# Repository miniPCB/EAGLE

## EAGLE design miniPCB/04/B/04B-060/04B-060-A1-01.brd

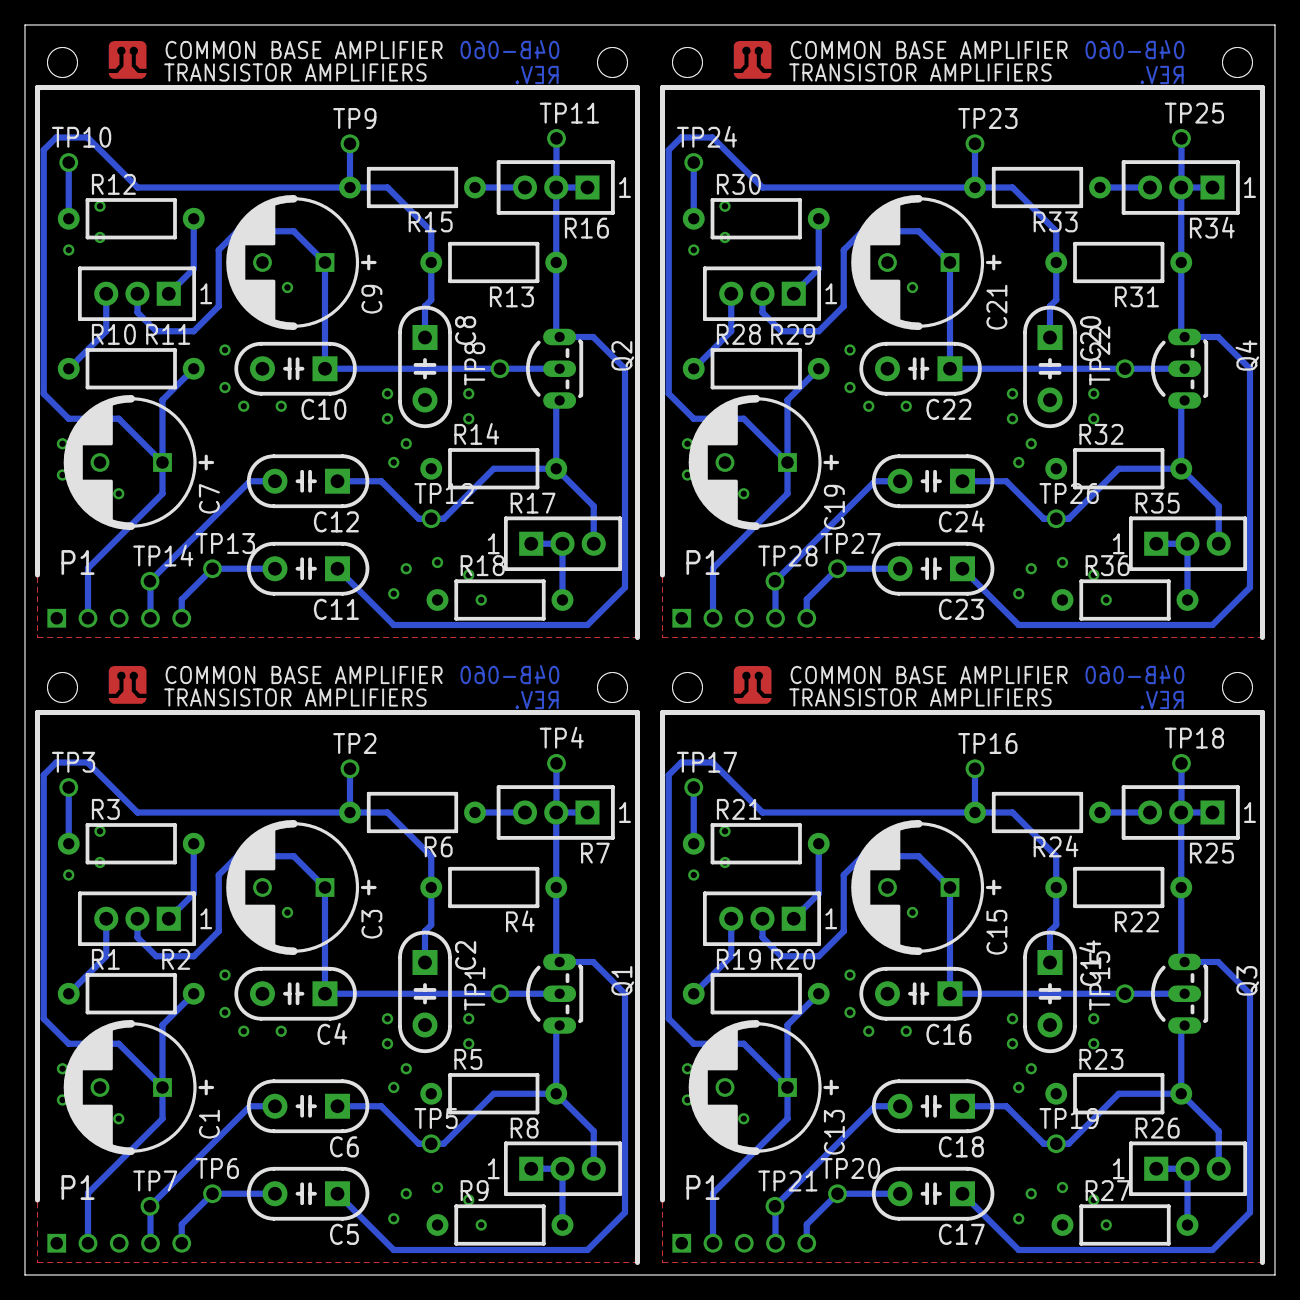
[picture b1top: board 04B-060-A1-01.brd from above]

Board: 2 copper layers, 100.0 x 100.0 mm, 100 parts (0 on the bottom side), 44 nets.

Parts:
C1, C3, C7, C9, C13, C15, C19, C21: C5MM
C2, C4, C5, C6, C8, C10, C11, C12, C14, C16, C17, C18, C20, C22, C23, C24: C050-024X044
P1, P2, P3, P4: PINS_1X5
PCB1, PCB2, PCB3, PCB4: MINIPCB_0P_50X50MM
Q1, Q2, Q3, Q4: NPN; TO92-EBC-OVAL
R1, R3, R4, R5, R6, R9, R10, R12, R13, R14, R15, R18, R19, R21, R22, R23, R24, R27, R28, R30, R31, R32, R33, R36: 0204/10
R2, R7, R8, R11, R16, R17, R20, R25, R26, R29, R34, R35: TRIM_0100
TP1, TP2, TP3, TP4, TP5, TP6, TP7, TP8, TP9, TP10, TP11, TP12, TP13, TP14, TP15, TP16, TP17, TP18, TP19, TP20, TP21, TP22, TP23, TP24, TP25, TP26, TP27, TP28: PINS_1_TESTPOINT_KE5000_NOTEXT

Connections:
BASE: C3.+, C4.1, Q1.B, R2.2, TP1.1
BASE1: C9.+, C10.1, Q2.B, R11.2, TP8.1
BASE2: C15.+, C16.1, Q3.B, R20.2, TP15.1
BASE3: C21.+, C22.1, Q4.B, R29.2, TP22.1
COLLECTOR: C5.1, Q1.C, R4.1, R7.1, R7.2, TP4.1
COLLECTOR1: C11.1, Q2.C, R13.1, R16.1, R16.2, TP11.1
COLLECTOR2: C17.1, Q3.C, R22.1, R25.1, R25.2, TP18.1
COLLECTOR3: C23.1, Q4.C, R31.1, R34.1, R34.2, TP25.1
EMITTER: C6.1, Q1.E, R5.2, R8.3, TP5.1
EMITTER1: C12.1, Q2.E, R14.2, R17.3, TP12.1
EMITTER2: C18.1, Q3.E, R23.2, R26.3, TP19.1
EMITTER3: C24.1, Q4.E, R32.2, R35.3, TP26.1
GND: C1.-, C2.2, C3.-, C4.2, P1.1, R3.1, R5.1, R9.1, TP3.1
GND1: C7.-, C8.2, C9.-, C10.2, P2.1, R12.1, R14.1, R18.1, TP10.1
GND2: C13.-, C14.2, C15.-, C16.2, P3.1, R21.1, R23.1, R27.1, TP17.1
GND3: C19.-, C20.2, C21.-, C22.2, P4.1, R30.1, R32.1, R36.1, TP24.1
INPUT: C6.2, P1.4, TP7.1
INPUT1: C12.2, P2.4, TP14.1
INPUT2: C18.2, P3.4, TP21.1
INPUT3: C24.2, P4.4, TP28.1
unnamed: R2.1, R3.2
unnamed: R1.1, R2.3
unnamed: R8.1, R8.2, R9.2
unnamed: R6.1, R7.3
unnamed: R11.1, R12.2
unnamed: R10.1, R11.3
unnamed: R15.1, R16.3
unnamed: R17.1, R17.2, R18.2
unnamed: R20.1, R21.2
unnamed: R19.1, R20.3
unnamed: R24.1, R25.3
unnamed: R26.1, R26.2, R27.2
unnamed: R29.1, R30.2
unnamed: R28.1, R29.3
unnamed: R33.1, R34.3
unnamed: R35.1, R35.2, R36.2
OUTPUT: C5.2, P1.5, TP6.1
OUTPUT1: C11.2, P2.5, TP13.1
OUTPUT2: C17.2, P3.5, TP20.1
OUTPUT3: C23.2, P4.5, TP27.1
V+: C1.+, C2.1, P1.2, R1.2, R4.2, R6.2, TP2.1
V+1: C7.+, C8.1, P2.2, R10.2, R13.2, R15.2, TP9.1
V+2: C13.+, C14.1, P3.2, R19.2, R22.2, R24.2, TP16.1
V+3: C19.+, C20.1, P4.2, R28.2, R31.2, R33.2, TP23.1

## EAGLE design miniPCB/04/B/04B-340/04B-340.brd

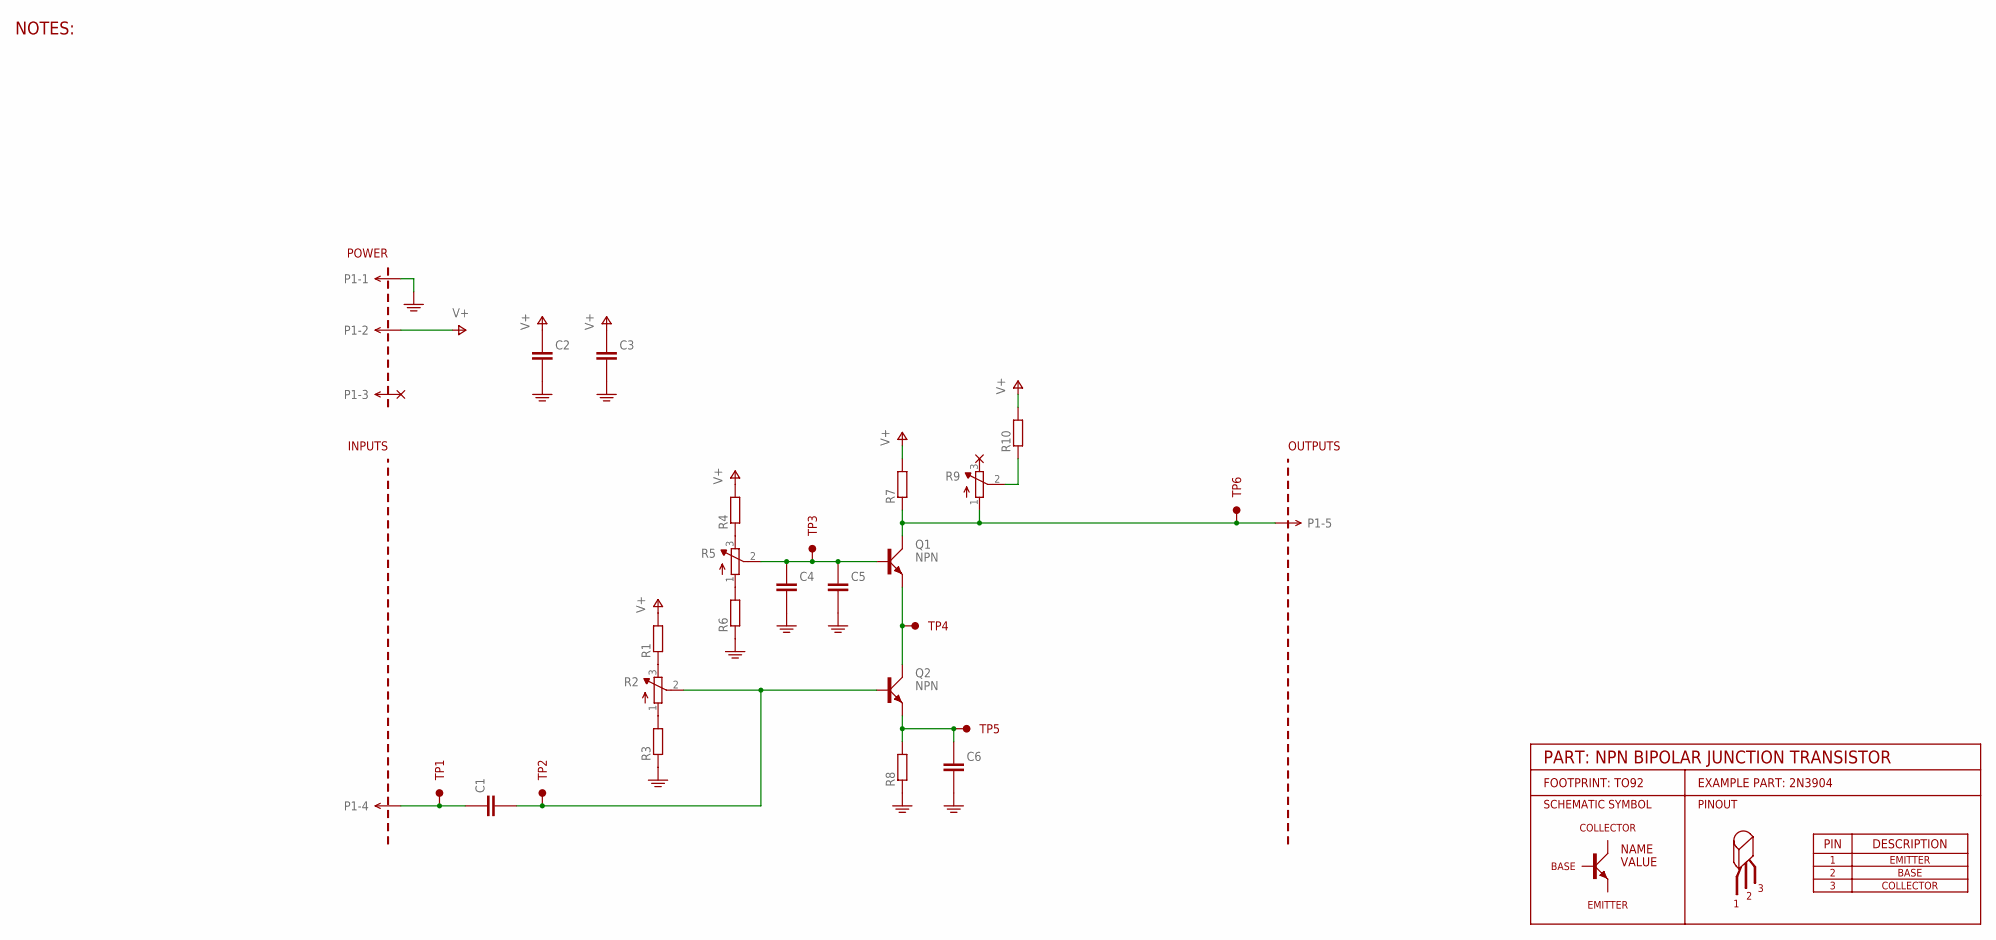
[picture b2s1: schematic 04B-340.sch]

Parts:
C1, C3, C4: CAPACITORTHD; C050-024X044
C2, C5, C6: CAPACITOR_10; C5MM
P1: MINIPCB_5P5P; PINS_1X5
PCB1: MINIPCB_0P50X50; MINIPCB_0P_50X50MM; PART_NUMBER 04B-340
Q1, Q2: NPN; TO92-EBC-OVAL
R1, R3, R4, R6, R7, R8, R10: RESISTORTHD; 0204/10
R2, R5, R9: TRIMPOT0.100THD; TRIM_0100
TP1, TP2, TP3, TP4, TP5, TP6: TESTPOINTKE5000-SMTEXT; PINS_1_TESTPOINT_KE5000_NOTEXT

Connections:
GND: C2.-, C3.2 (-), C4.2 (-), C5.-, C6.-, P1.1, R3.1, R6.1, R8.1
unnamed: R2.1 (A), R3.2
unnamed: C1.2 (-), Q2.B, R2.2 (S), TP2.1
unnamed: C4.1 (+), C5.+, Q1.B, R5.2 (S), TP3.1
unnamed: R1.1, R2.3 (E)
unnamed: R4.1, R5.3 (E)
unnamed: R5.1 (A), R6.2
unnamed: C1.1 (+), P1.4, TP1.1
unnamed: Q1.E, Q2.C, TP4.1
unnamed: P1.5, Q1.C, R7.1, R9.1 (A), TP6.1
unnamed: C6.+, Q2.E, R8.2, TP5.1
unnamed: R9.2 (S), R10.1
V+: C2.+, C3.1 (+), P1.2, R1.2, R4.2, R7.2, R10.2

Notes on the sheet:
NOTES:

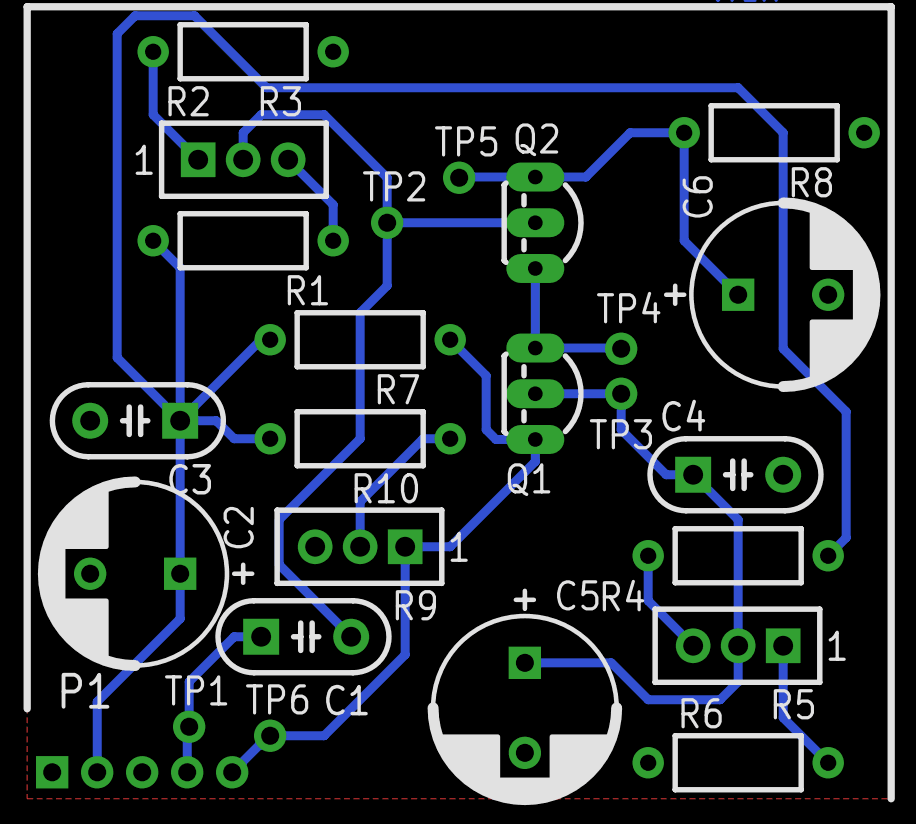
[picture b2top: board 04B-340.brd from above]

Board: 2 copper layers, 26 parts (0 on the bottom side), 13 nets.

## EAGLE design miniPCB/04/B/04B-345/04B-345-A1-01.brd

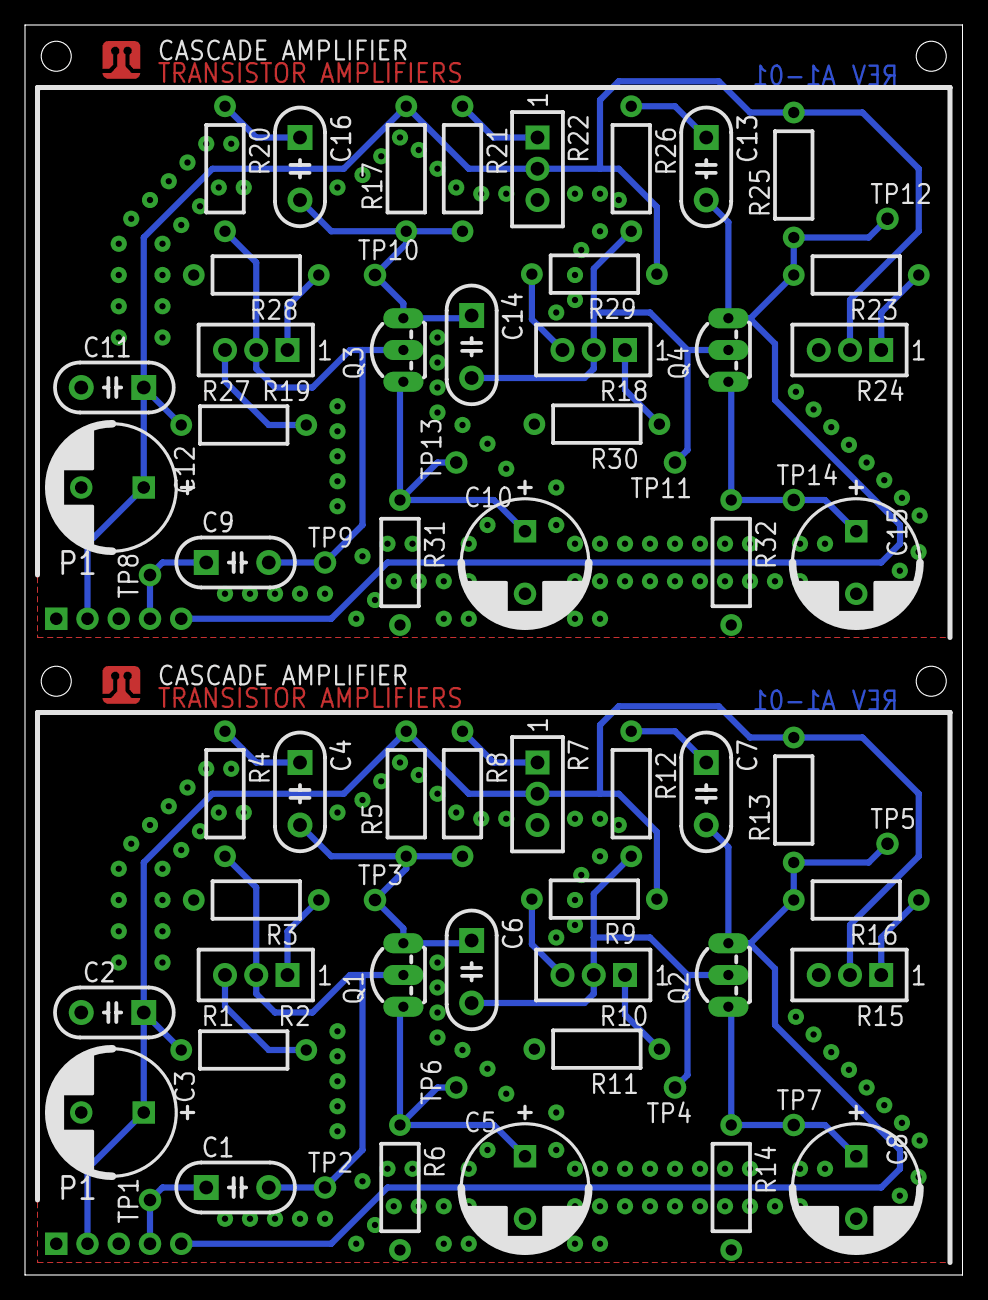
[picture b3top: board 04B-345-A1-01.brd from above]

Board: 2 copper layers, 75.0 x 100.0 mm, 70 parts (0 on the bottom side), 34 nets.

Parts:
C1, C2, C4, C6, C7, C9, C11, C13, C14, C16: C050-024X044
C3, C5, C8, C10, C12, C15: C5MM
P1, P2: PINS_1X5
PCB1, PCB2: MINIPCB_0P_50X75
Q1, Q2, Q3, Q4: TO92-EBC-OVAL
R1, R3, R4, R5, R6, R8, R9, R11, R12, R13, R14, R16, R17, R20, R21, R23, R25, R26, R27, R28, R29, R30, R31, R32: 0204/10
R2, R7, R10, R15, R18, R19, R22, R24: TRIM_0100
TP1, TP2, TP3, TP4, TP5, TP6, TP7, TP8, TP9, TP10, TP11, TP12, TP13, TP14: PINS_1_TESTPOINT_KE5000_NOTEXT

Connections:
GND: C2.2, C3.-, C5.-, C8.-, P1.1, R3.2, R6.2, R11.2, R14.2
GND1: C10.-, C11.2, C12.-, C15.-, P2.1, R28.2, R30.2, R31.2, R32.2
unnamed: C4.2, C6.1, Q1.C, R5.1, R8.2, TP3.1
unnamed: C5.+, Q1.E, R6.1, TP6.1
unnamed: C7.2, P1.5, Q2.C, R13.1, R16.2, TP5.1
unnamed: C8.+, Q2.E, R14.1, TP7.1
unnamed: C7.1, R12.1
unnamed: C6.2, Q2.B, R10.2, R12.2, TP4.1
unnamed: R1.2, R2.3
unnamed: R2.1, R3.1
unnamed: C1.2, Q1.B, R2.2, R4.2, TP2.1
unnamed: C4.1, R4.1
unnamed: R9.2, R10.3
unnamed: R10.1, R11.1
unnamed: C1.1, P1.4, TP1.1
unnamed: R7.1, R8.1
unnamed: R15.1, R16.1
unnamed: C14.1, C16.2, Q3.C, R17.1, R21.2, TP10.1
unnamed: C10.+, Q3.E, R31.1, TP13.1
unnamed: C13.2, P2.5, Q4.C, R23.2, R25.1, TP12.1
unnamed: C15.+, Q4.E, R32.1, TP14.1
unnamed: C13.1, R26.1
unnamed: C14.2, Q4.B, R18.2, R26.2, TP11.1
unnamed: R19.3, R27.2
unnamed: R19.1, R28.1
unnamed: C9.2, Q3.B, R19.2, R20.2, TP9.1
unnamed: R18.3, R29.2
unnamed: R18.1, R30.1
unnamed: C9.1, P2.4, TP8.1
unnamed: C16.1, R20.1
unnamed: R21.1, R22.1
unnamed: R23.1, R24.1
V+: C2.1, C3.+, P1.2, R1.1, R5.2, R7.2, R9.1, R13.2, R15.2
V+1: C11.1, C12.+, P2.2, R17.2, R22.2, R24.2, R25.2, R27.1, R29.1

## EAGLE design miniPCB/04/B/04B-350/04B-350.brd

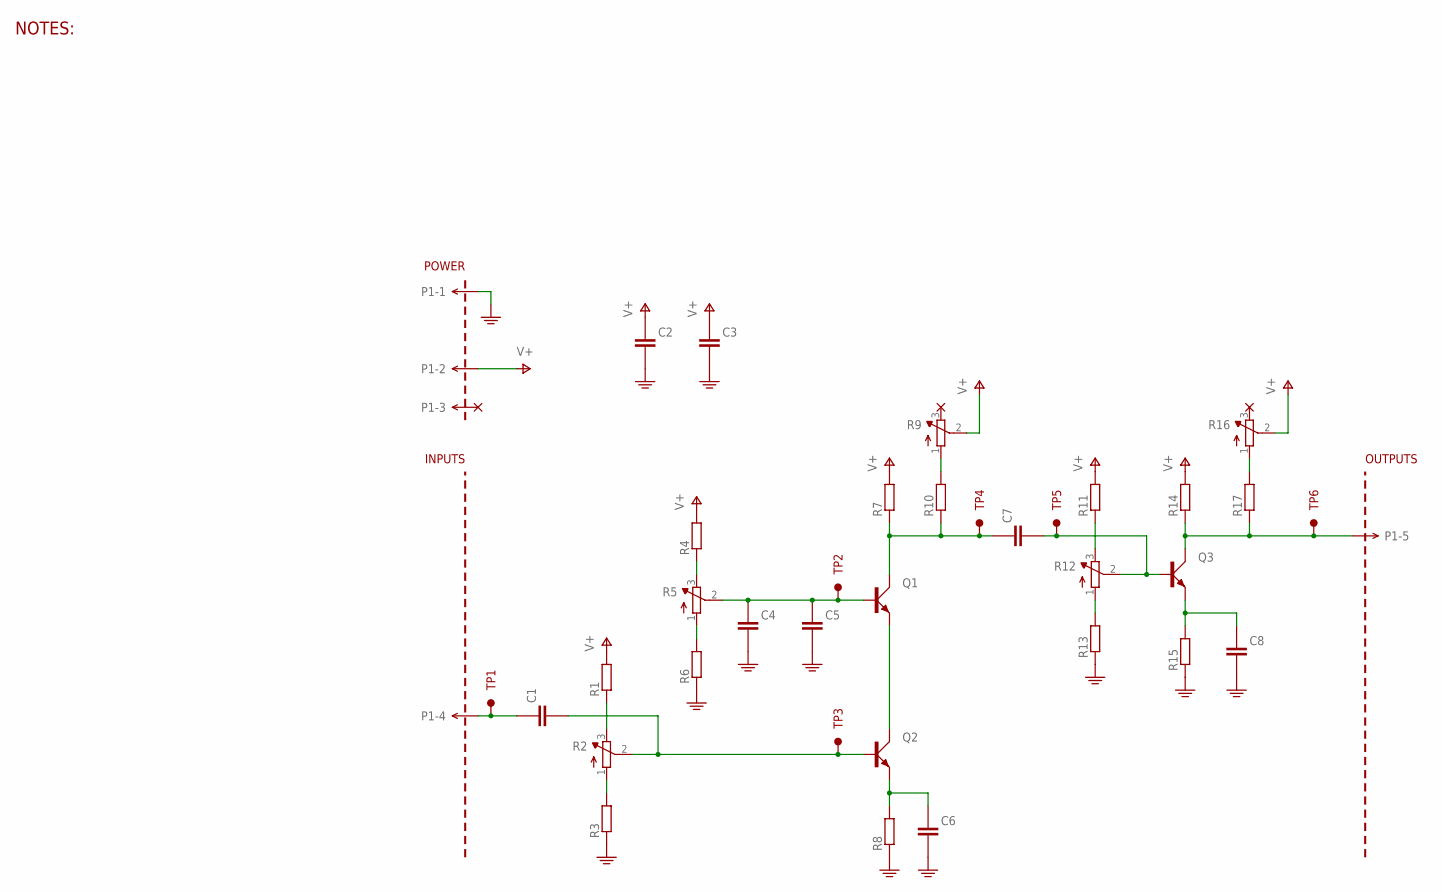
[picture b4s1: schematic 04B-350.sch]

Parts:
C1, C2, C5, C7: CAPACITORTHD; C050-024X044
C3, C4, C6, C8: CAPACITOR_10; C5MM
P1: MINIPCB_5P5P; PINS_1X5
PCB1: MINIPCB_0P50X75; MINIPCB_0P_50X75; PART_NUMBER 04B-350
Q1, Q2, Q3: BJT_NPNEBC; TO92-EBC-OVAL
R1, R3, R4, R6, R7, R8, R10, R11, R13, R14, R15, R17: RESISTORTHD; 0204/10
R2, R5, R9, R12, R16: TRIMPOT0.100THD; TRIM_0100
TP1, TP2, TP3, TP4, TP5, TP6: TESTPOINTKE5000-SMTEXT; PINS_1_TESTPOINT_KE5000_NOTEXT

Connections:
GND: C2.2 (-), C3.-, C4.-, C5.2 (-), C6.-, C8.-, P1.1, R3.1, R6.1, R8.1, R13.1, R15.1
unnamed: C4.+, C5.1 (+), Q1.B, R5.2 (S), TP2.1
unnamed: R4.1, R5.3 (E)
unnamed: R5.1 (A), R6.2
unnamed: Q1.E, Q2.C
unnamed: C1.2 (-), Q2.B, R2.2 (S), TP3.1
unnamed: R1.1, R2.3 (E)
unnamed: R2.1 (A), R3.2
unnamed: R12.1 (A), R13.2
unnamed: C8.+, Q3.E, R15.2
unnamed: P1.5, Q3.C, R14.1, R17.1, TP6.1
unnamed: R11.1, R12.3 (E)
unnamed: C6.+, Q2.E, R8.2
unnamed: C7.2 (-), Q3.B, R12.2 (S), TP5.1
unnamed: C1.1 (+), P1.4, TP1.1
unnamed: C7.1 (+), Q1.C, R7.1, R10.1, TP4.1
unnamed: R9.1 (A), R10.2
unnamed: R16.1 (A), R17.2
V+: C2.1 (+), C3.+, P1.2, R1.2, R4.2, R7.2, R9.2 (S), R11.2, R14.2, R16.2 (S)

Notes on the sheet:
NOTES:

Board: 2 copper layers, 36 parts (0 on the bottom side), 19 nets, no tracks yet.

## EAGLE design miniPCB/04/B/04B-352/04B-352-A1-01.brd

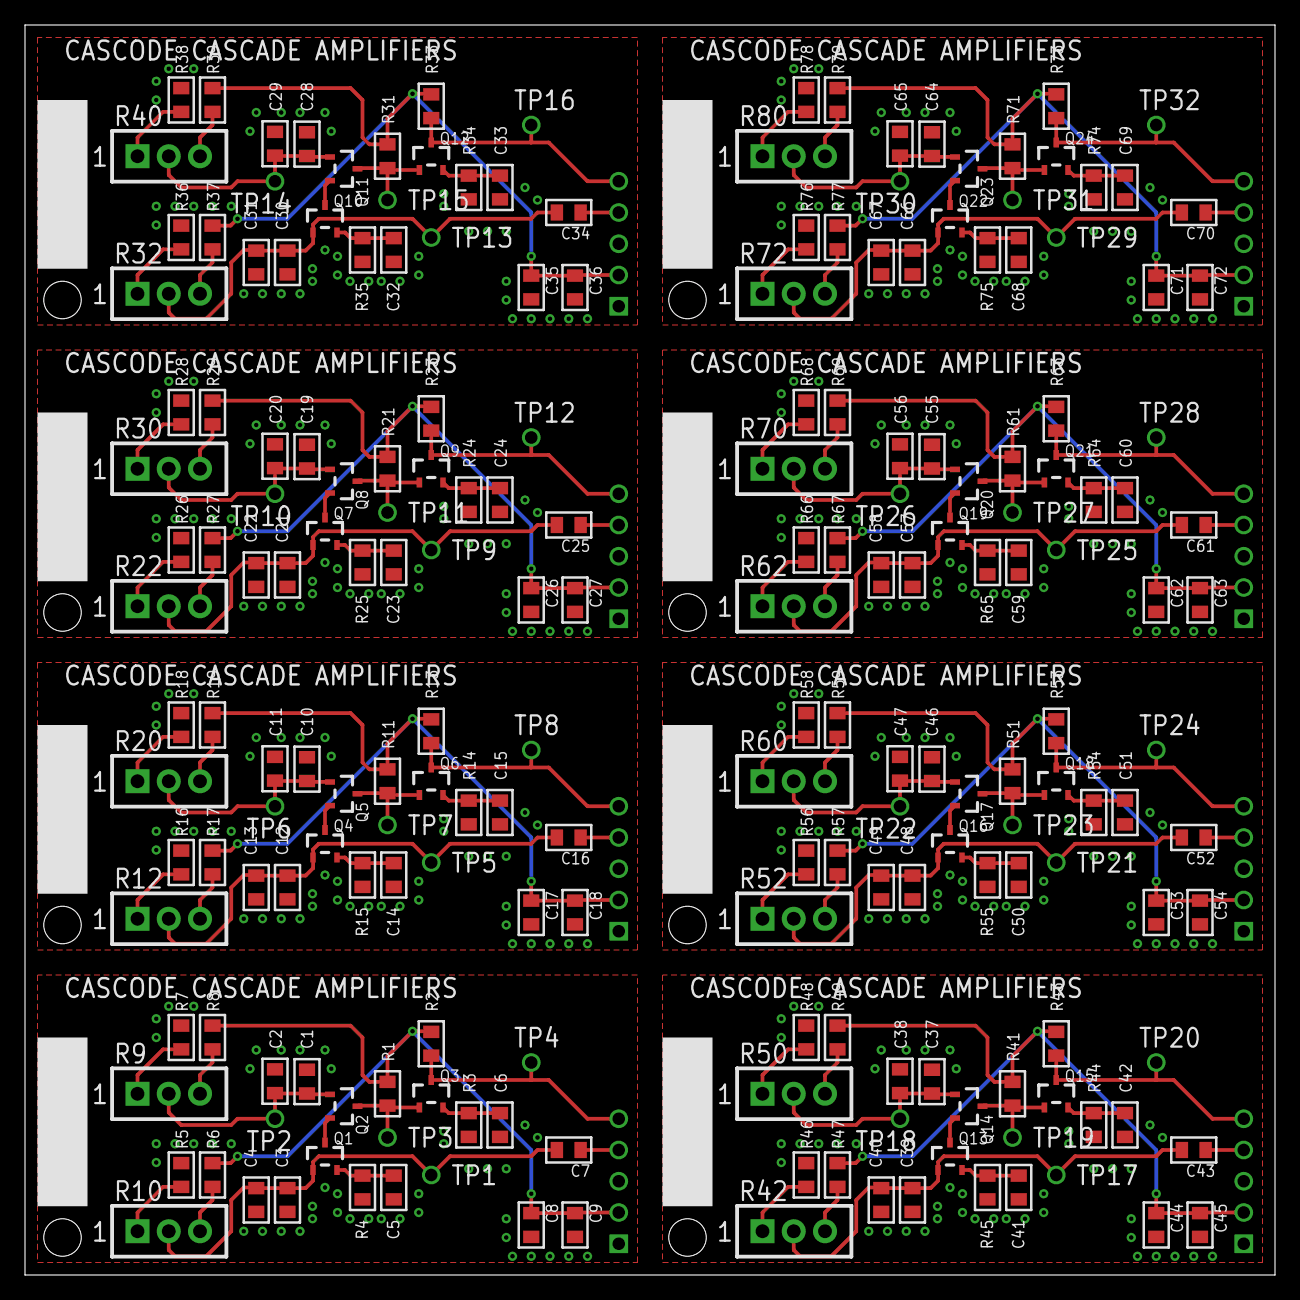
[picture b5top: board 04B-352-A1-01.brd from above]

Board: 4 copper layers, 100.0 x 100.0 mm, 225 parts (0 on the bottom side), 112 nets.

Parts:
C1, C2, C3, C4, C5, C6, C7, C8, C9, C10, C11, C12, C13, C14, C15, C16, C17, C18, C19, C20, C21, C22, C23, C24, C25, C26, C27, C28, C29, C30, C31, C32, C33, C34, C35, C36, C37, C38, C39, C40, C41, C42, C43, C44, C45, C46, C47, C48, C49, C50, C51, C52, C53, C54, C55, C56, C57, C58, C59, C60, C61, C62, C63, C64, C65, C66, C67, C68, C69, C70, C71, C72: C0805
E$1: MINIPCB_PANEL_IMAGEFRAME
P1, P2, P3, P4, P5, P6, P7, P8: PINS_1X5
PCB1, PCB2, PCB3, PCB4, PCB5, PCB6, PCB7, PCB8: MINIPCB_0P_25X50
Q1, Q2, Q3, Q4, Q5, Q6, Q7, Q8, Q9, Q10, Q11, Q12, Q13, Q14, Q15, Q16, Q17, Q18, Q19, Q20, Q21, Q22, Q23, Q24: SOT23
R1, R2, R3, R4, R5, R6, R7, R8, R11, R13, R14, R15, R16, R17, R18, R19, R21, R23, R24, R25, R26, R27, R28, R29, R31, R33, R34, R35, R36, R37, R38, R39, R41, R43, R44, R45, R46, R47, R48, R49, R51, R53, R54, R55, R56, R57, R58, R59, R61, R63, R64, R65, R66, R67, R68, R69, R71, R73, R74, R75, R76, R77, R78, R79: R0805
R9, R10, R12, R20, R22, R30, R32, R40, R42, R50, R52, R60, R62, R70, R72, R80: TRIM_0100
TP1, TP2, TP3, TP4, TP5, TP6, TP7, TP8, TP9, TP10, TP11, TP12, TP13, TP14, TP15, TP16, TP17, TP18, TP19, TP20, TP21, TP22, TP23, TP24, TP25, TP26, TP27, TP28, TP29, TP30, TP31, TP32: PINS_1_TESTPOINT_KE5000_NOTEXT

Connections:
GND: C1.2, C2.2, C3.2, C4.2, C5.2, C6.2, C8.2, C9.2, P1.1, R3.1, R4.1, R5.2, R7.2
GND1: C10.2, C11.2, C12.2, C13.2, C14.2, C15.2, C17.2, C18.2, P2.1, R14.1, R15.1, R16.2, R18.2
GND2: C19.2, C20.2, C21.2, C22.2, C23.2, C24.2, C26.2, C27.2, P3.1, R24.1, R25.1, R26.2, R28.2
GND3: C28.2, C29.2, C30.2, C31.2, C32.2, C33.2, C35.2, C36.2, P4.1, R34.1, R35.1, R36.2, R38.2
GND4: C37.2, C38.2, C39.2, C40.2, C41.2, C42.2, C44.2, C45.2, P5.1, R44.1, R45.1, R46.2, R48.2
GND5: C46.2, C47.2, C48.2, C49.2, C50.2, C51.2, C53.2, C54.2, P6.1, R54.1, R55.1, R56.2, R58.2
GND6: C55.2, C56.2, C57.2, C58.2, C59.2, C60.2, C62.2, C63.2, P7.1, R64.1, R65.1, R66.2, R68.2
GND7: C64.2, C65.2, C66.2, C67.2, C68.2, C69.2, C71.2, C72.2, P8.1, R74.1, R75.1, R76.2, R78.2
unnamed: R6.2, R10.3
unnamed: R5.1, R10.1
unnamed: R7.1, R9.1
unnamed: R8.2, R9.3
unnamed: C1.1, C2.1, Q2.1, R9.2, TP2.1
unnamed: C3.1, C4.1, C7.2, Q1.1, R10.2, TP1.1
unnamed: C5.1, Q1.2, R4.2
unnamed: C6.1, Q3.2, R3.2
unnamed: Q1.3, Q2.2
unnamed: Q2.3, Q3.1, R1.1, TP3.1
unnamed: C7.1, P1.4
unnamed: P1.5, Q3.3, R2.1, TP4.1
unnamed: R12.3, R17.2
unnamed: R12.1, R16.1
unnamed: R18.1, R20.1
unnamed: R19.2, R20.3
unnamed: C10.1, C11.1, Q5.1, R20.2, TP6.1
unnamed: C12.1, C13.1, C16.2, Q4.1, R12.2, TP5.1
unnamed: C14.1, Q4.2, R15.2
unnamed: Q4.3, Q5.2
unnamed: Q5.3, Q6.1, R11.1, TP7.1
unnamed: C15.1, Q6.2, R14.2
unnamed: P2.5, Q6.3, R13.1, TP8.1
unnamed: C16.1, P2.4
unnamed: R22.3, R27.2
unnamed: R22.1, R26.1
unnamed: R28.1, R30.1
unnamed: R29.2, R30.3
unnamed: C19.1, C20.1, Q8.1, R30.2, TP10.1
unnamed: C21.1, C22.1, C25.2, Q7.1, R22.2, TP9.1
unnamed: C23.1, Q7.2, R25.2
unnamed: Q7.3, Q8.2
unnamed: Q8.3, Q9.1, R21.1, TP11.1
unnamed: C24.1, Q9.2, R24.2
unnamed: P3.5, Q9.3, R23.1, TP12.1
unnamed: C25.1, P3.4
unnamed: R32.3, R37.2
unnamed: R32.1, R36.1
unnamed: R38.1, R40.1
unnamed: R39.2, R40.3
unnamed: C28.1, C29.1, Q11.1, R40.2, TP14.1
unnamed: C30.1, C31.1, C34.2, Q10.1, R32.2, TP13.1
unnamed: C32.1, Q10.2, R35.2
unnamed: Q10.3, Q11.2
unnamed: Q11.3, Q12.1, R31.1, TP15.1
unnamed: C33.1, Q12.2, R34.2
unnamed: P4.5, Q12.3, R33.1, TP16.1
unnamed: C34.1, P4.4
unnamed: R42.3, R47.2
unnamed: R42.1, R46.1
unnamed: R48.1, R50.1
unnamed: R49.2, R50.3
unnamed: C37.1, C38.1, Q14.1, R50.2, TP18.1
unnamed: C39.1, C40.1, C43.2, Q13.1, R42.2, TP17.1
unnamed: C41.1, Q13.2, R45.2
unnamed: Q13.3, Q14.2
unnamed: Q14.3, Q15.1, R41.1, TP19.1
unnamed: C42.1, Q15.2, R44.2
unnamed: P5.5, Q15.3, R43.1, TP20.1
unnamed: C43.1, P5.4
unnamed: R52.3, R57.2
unnamed: R52.1, R56.1
unnamed: R58.1, R60.1
unnamed: R59.2, R60.3
unnamed: C46.1, C47.1, Q17.1, R60.2, TP22.1
unnamed: C48.1, C49.1, C52.2, Q16.1, R52.2, TP21.1
unnamed: C50.1, Q16.2, R55.2
unnamed: Q16.3, Q17.2
unnamed: Q17.3, Q18.1, R51.1, TP23.1
unnamed: C51.1, Q18.2, R54.2
unnamed: P6.5, Q18.3, R53.1, TP24.1
unnamed: C52.1, P6.4
unnamed: R62.3, R67.2
unnamed: R62.1, R66.1
unnamed: R68.1, R70.1
unnamed: R69.2, R70.3
unnamed: C55.1, C56.1, Q20.1, R70.2, TP26.1
unnamed: C57.1, C58.1, C61.2, Q19.1, R62.2, TP25.1
unnamed: C59.1, Q19.2, R65.2
unnamed: Q19.3, Q20.2
unnamed: Q20.3, Q21.1, R61.1, TP27.1
unnamed: C60.1, Q21.2, R64.2
unnamed: P7.5, Q21.3, R63.1, TP28.1
unnamed: C61.1, P7.4
unnamed: R72.3, R77.2
unnamed: R72.1, R76.1
unnamed: R78.1, R80.1
unnamed: R79.2, R80.3
unnamed: C64.1, C65.1, Q23.1, R80.2, TP30.1
unnamed: C66.1, C67.1, C70.2, Q22.1, R72.2, TP29.1
unnamed: C68.1, Q22.2, R75.2
unnamed: Q22.3, Q23.2
unnamed: Q23.3, Q24.1, R71.1, TP31.1
unnamed: C69.1, Q24.2, R74.2
unnamed: P8.5, Q24.3, R73.1, TP32.1
unnamed: C70.1, P8.4
V+: C8.1, C9.1, P1.2, R1.2, R2.2, R6.1, R8.1
V+1: C17.1, C18.1, P2.2, R11.2, R13.2, R17.1, R19.1
V+2: C26.1, C27.1, P3.2, R21.2, R23.2, R27.1, R29.1
V+3: C35.1, C36.1, P4.2, R31.2, R33.2, R37.1, R39.1
V+4: C44.1, C45.1, P5.2, R41.2, R43.2, R47.1, R49.1
V+5: C53.1, C54.1, P6.2, R51.2, R53.2, R57.1, R59.1
V+6: C62.1, C63.1, P7.2, R61.2, R63.2, R67.1, R69.1
V+7: C71.1, C72.1, P8.2, R71.2, R73.2, R77.1, R79.1
